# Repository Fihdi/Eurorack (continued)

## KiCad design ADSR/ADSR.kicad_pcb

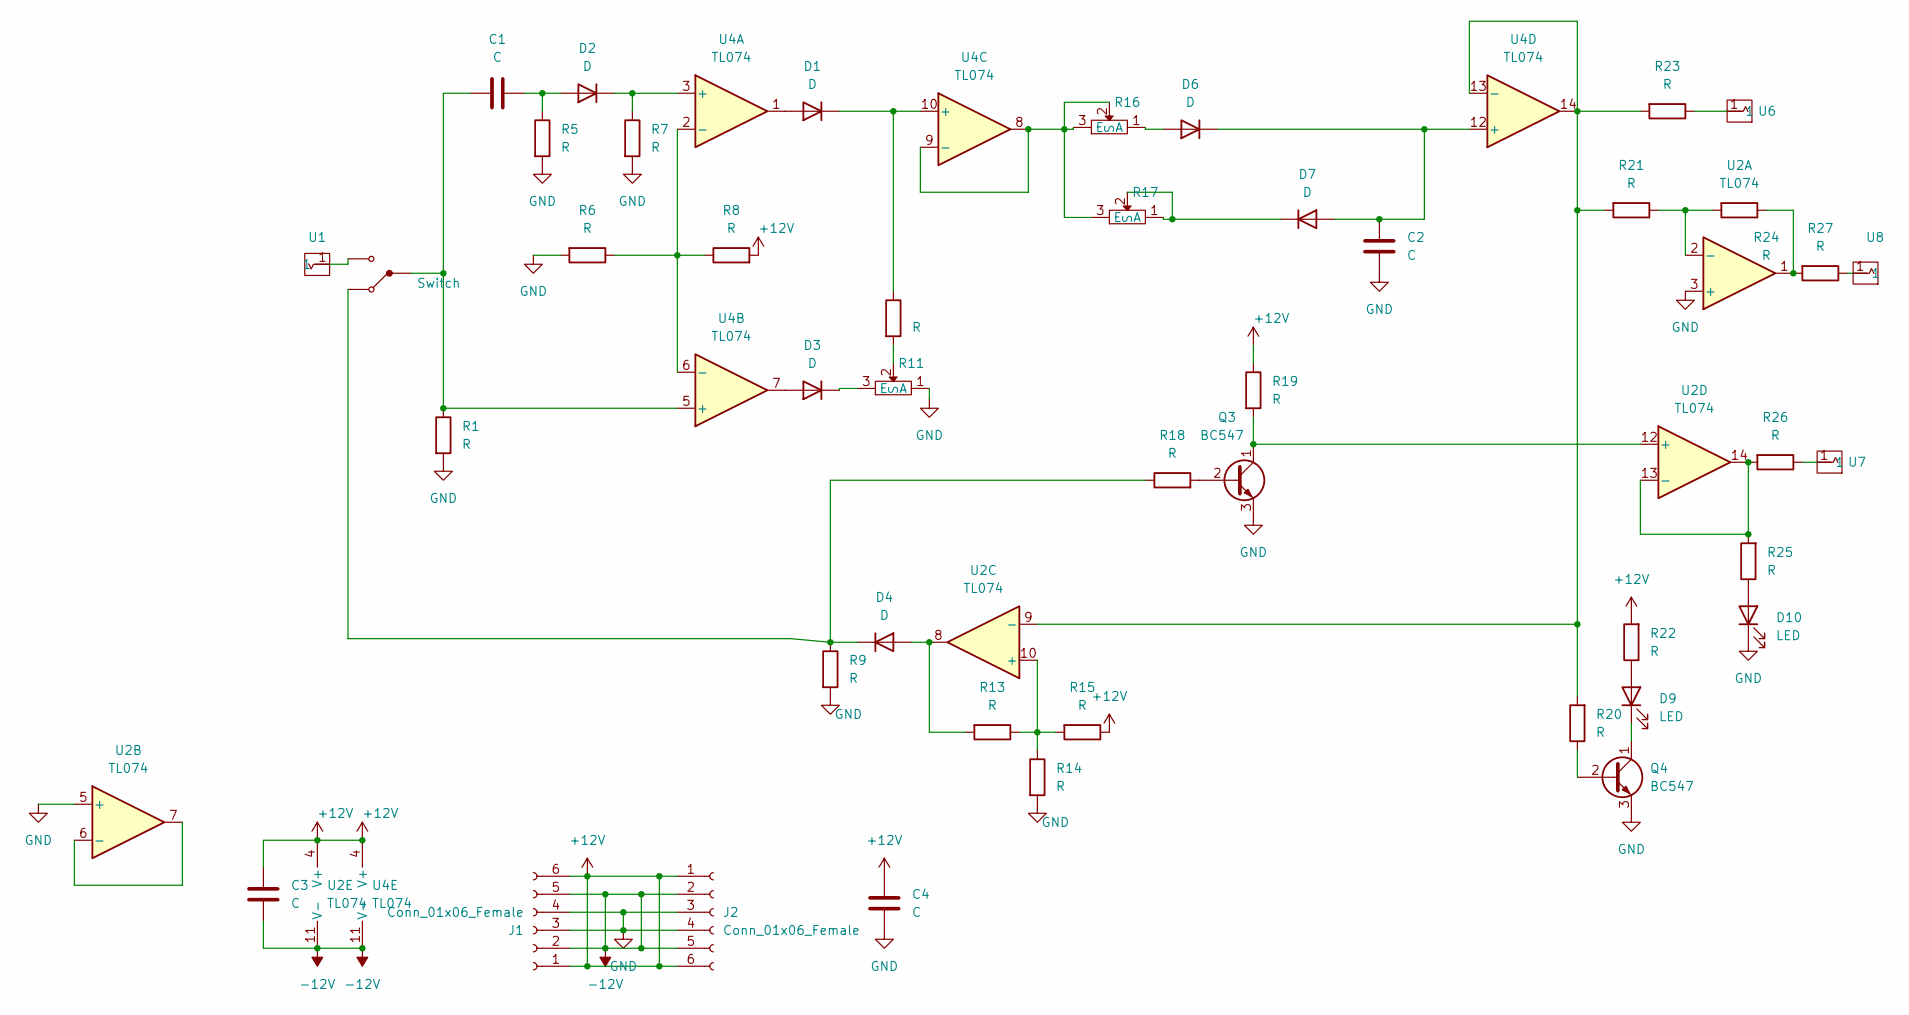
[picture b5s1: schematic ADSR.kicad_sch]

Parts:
C1, C3: C; C_Axial_L3.8mm_D2.6mm_P7.50mm_Horizontal
C2, C4: C; C_Axial_L3.8mm_D2.6mm_P10.00mm_Horizontal
D1, D2, D3, D4, D6, D7: D; D_A-405_P5.08mm_Vertical_AnodeUp
D9, D10: LED; LED_D5.0mm
J1, J2: Conn_01x06_Female; PinHeader_1x06_P2.54mm_Vertical
Q3, Q4: BC547; TO-92L_Inline_Wide
R1, R5, R6, R7, R8, R9, R10, R13, R14, R15, R18, R19, R20, R21, R22, R23, R24, R25, R26, R27: R; R_Axial_DIN0204_L3.6mm_D1.6mm_P7.62mm_Horizontal
R11, R16, R17: AlpsPot
U1, U6, U7, U8: Aux_flush; aux_flush
U2, U4: TL074; DIP-14_W7.62mm
U3: Switch

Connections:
+12V: C3.2, C4.2, J1.1, J1.6, J2.1, J2.6, R8.2, R15.1, R19.1, R22.2, U2.4 (V+), U4.4 (V+)
-12V: C3.1, J1.2, J1.5, J2.2, J2.5, U2.11 (V-), U4.11 (V-)
GND: C2.1, C4.1, D10.1 (K), J1.3, J1.4, J2.3, J2.4, Q3.3 (E), Q4.3 (E), R1.2, R5.2, R6.2, R7.2, R9.2, R11.1 (A), R14.2, U2.3 (+), U2.5 (+)
unnamed: D1.2 (A), U4.1
unnamed: D1.1 (K), R10.1, U4.10 (+)
unnamed: C1.2, D2.2 (A), R5.1
unnamed: D2.1 (K), R7.1, U4.3 (+)
unnamed: D3.2 (A), U4.7
unnamed: D3.1 (K), R11.3 (E)
unnamed: D4.2 (A), R13.2, U2.8
unnamed: D4.1 (K), R9.1, R18.1, U3.1
unnamed: D6.2 (A), R16.1 (A)
unnamed: C2.2, D6.1 (K), D7.2 (A), U4.12 (+)
unnamed: D7.1 (K), R17.1 (A), R17.2 (S)
unnamed: D9.2 (A), R22.1
unnamed: D9.1 (K), Q4.1 (C)
unnamed: D10.2 (A), R25.1
unnamed: Q3.2 (B), R18.2
unnamed: Q3.1 (C), R19.2, U2.12 (+)
unnamed: Q4.2 (B), R20.1
unnamed: R10.2, R11.2 (S)
unnamed: R16.2 (S), R16.3 (E), R17.3 (E), U4.8, U4.9 (-)
unnamed: R23.1, U6.1
unnamed: R24.1, R27.2, U2.1
unnamed: R26.1, U7.1
unnamed: R27.1, U8.1
unnamed: U1.1, U3.3
unnamed: R21.1, R24.2, U2.2 (-)
unnamed: U2.6 (-), U2.7
unnamed: R13.1, R14.1, R15.2, U2.10 (+)
unnamed: R20.2, R21.2, R23.2, U2.9 (-), U4.13 (-), U4.14
unnamed: R25.2, R26.2, U2.13 (-), U2.14
unnamed: R6.1, R8.1, U4.2 (-), U4.6 (-)
unnamed: C1.1, R1.1, U3.2, U4.5 (+)

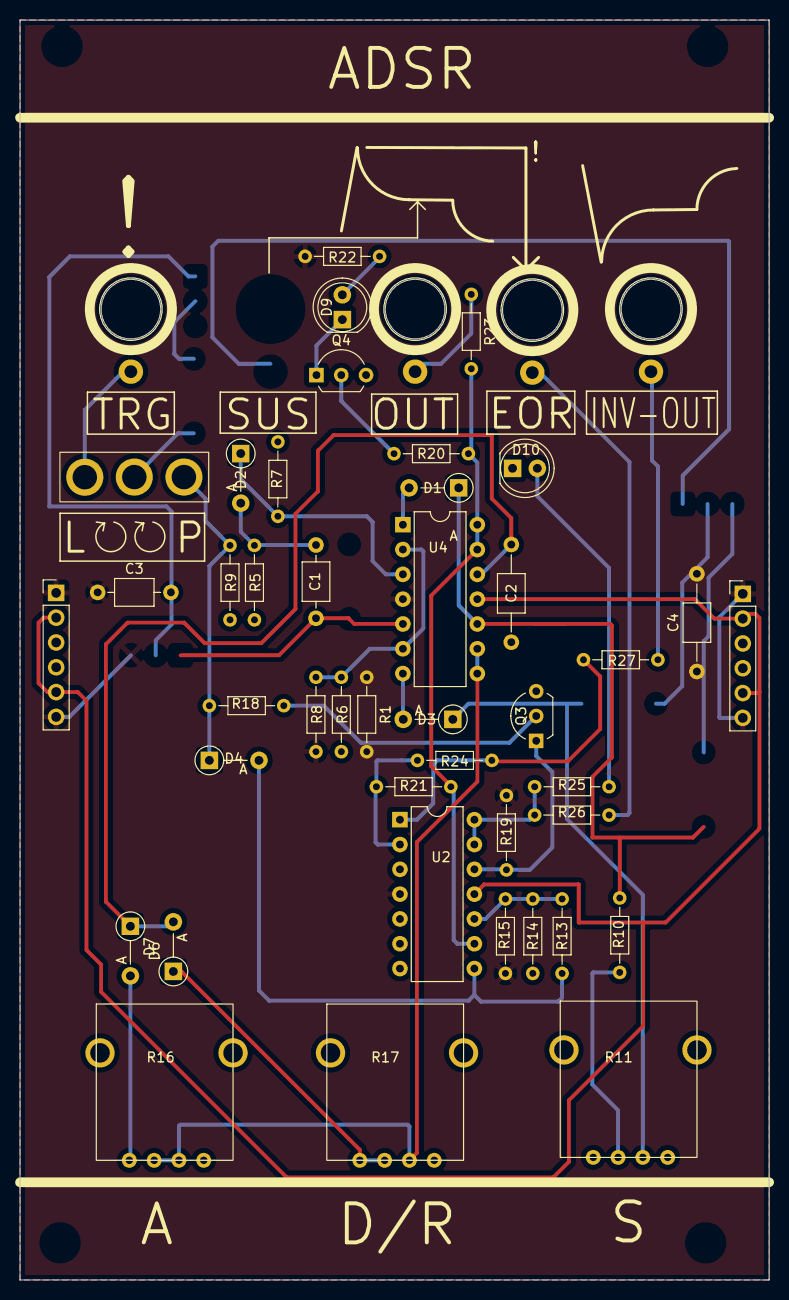
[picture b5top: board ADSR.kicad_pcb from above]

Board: 2 copper layers, 76.7 x 129.0 mm, 46 parts (0 on the bottom side), 34 nets.

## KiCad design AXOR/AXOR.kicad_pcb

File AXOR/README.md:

AXOR (Analogue XOR)

Improved stand-alone module of my analogue XOR circuit for CV intermangling, rectification or ring modulation purposes. XORing two square wave signals together results in an ringmodulation-like effect.

Incoming signals can be in the audio or in the low frequency range, including DC voltages. The signals are passed through VCAs before going to the AXOR circuit, these VCAs can also be bypassed via switches.

The core of this circuit is a subtractor followed by a full wave rectifier, the transfer function G for the CV OUT output is thus:

Example: IN1 and IN2 are square wave in the range of 0V - 5V:

The resulting truth table is the same as that of an XOR gate.

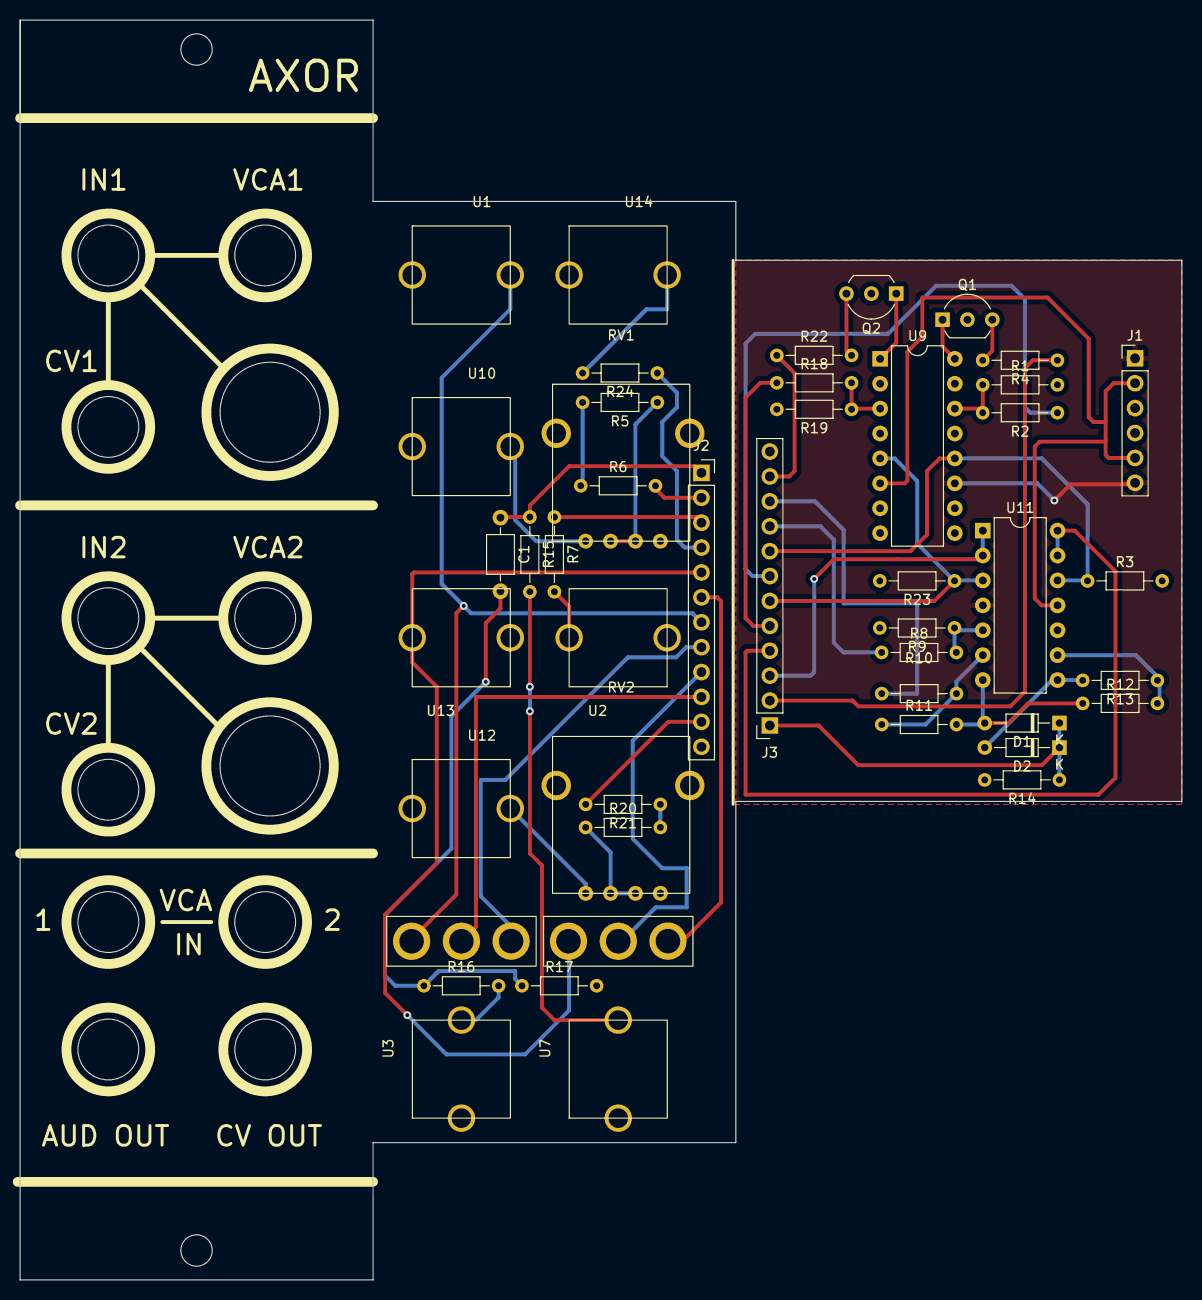
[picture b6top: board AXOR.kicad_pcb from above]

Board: 2 copper layers, 118.5 x 128.5 mm, 46 parts (0 on the bottom side), 36 nets.

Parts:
C1: 470n; C_Axial_L3.8mm_D2.6mm_P7.50mm_Horizontal
D1, D2: D; D_DO-34_SOD68_P7.62mm_Horizontal
J1: Conn_01x06_Pin; PinHeader_1x06_P2.54mm_Vertical
J2, J3: Conn_01x12_Pin; PinSocket_1x12_P2.54mm_Vertical
Q1, Q2: BC557; TO-92_Inline_Wide
R1, R5, R6, R7, R15, R16, R19, R20, R21, R24: 1k; R_Axial_DIN0204_L3.6mm_D1.6mm_P7.62mm_Horizontal
R2, R8, R9, R10, R11, R12, R13, R14, R17, R18: 100k; R_Axial_DIN0204_L3.6mm_D1.6mm_P7.62mm_Horizontal
R3, R4, R22, R23: 10k; R_Axial_DIN0204_L3.6mm_D1.6mm_P7.62mm_Horizontal
RV1, RV2: R_Potentiometer; AlpsPot
SW1, SW2: SW_SPDT; Switch
U1, U2, U3, U7, U10, U12, U13, U14: Aux_flush; 3mm5 Mono Aux
U9: LM13700; DIP-16_W7.62mm
U11: TL074; DIP-14_W7.62mm

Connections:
+12V: J1.1, J1.6, U9.11 (V+), U11.4 (V+)
-12V: J1.2, J1.5, U9.6 (V-), U11.11 (V-)
A1: J2.10, J3.10, R10.1, SW1.2 (B)
A2: J2.9, J3.9, R8.1, SW2.2 (B)
ABC1: J2.2, J3.2, R4.1, R6.2
ABC2: J2.11, J3.11, R21.2, R22.1
GND: J1.3, J1.4, J2.12, J3.12, Q1.2 (B), Q2.2 (B), R1.2, R3.2, R9.2, R14.2, R17.2, R19.2, R23.2, U9.4 (-), U9.13 (-), U11.10 (+)
IN1: J2.7, J3.7, R2.1, SW1.1 (A), U1.1
IN2: J2.5, J3.5, R18.1, SW2.1 (A), U13.1
unnamed: C1.2, R16.1, R17.1
unnamed: D1.2 (A), R11.2, R12.1, U11.7
unnamed: D2.2 (A), R13.2, U11.8
unnamed: Q1.1 (C), U9.16
unnamed: Q1.3 (E), R4.2
unnamed: Q2.1 (C), U9.1
unnamed: Q2.3 (E), R22.2
unnamed: R5.1, RV1.2, RV1.3
unnamed: R5.2, R6.1
unnamed: R7.2, U2.1
unnamed: R15.2, U7.1
unnamed: R16.2, U3.1
unnamed: R20.1, RV2.2, RV2.3
unnamed: R20.2, R21.1
unnamed: R24.2, U14.1
unnamed: RV1.1, U10.1
unnamed: RV2.1, U12.1
unnamed: R1.1, R2.2, U9.14 (+)
unnamed: R18.2, R19.1, U9.3 (+)
unnamed: R8.2, R9.1, U11.5 (+)
unnamed: R10.2, R11.1, U11.6 (-)
unnamed: R12.2, R13.1, U11.9 (-)
OUT: C1.1, D1.1 (K), D2.1 (K), J2.1, J3.1, R14.1, R15.1
OUT1: J2.4, J3.4, R24.1, U11.13 (-), U11.14
OUT2: J2.3, J3.3, R7.1, U11.1, U11.2 (-)
VCA1: J2.8, J3.8, R3.1, SW1.3 (C), U9.12, U11.12 (+)
VCA2: J2.6, J3.6, R23.1, SW2.3 (C), U9.5, U11.3 (+)

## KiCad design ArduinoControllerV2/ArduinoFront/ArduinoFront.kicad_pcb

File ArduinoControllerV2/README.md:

Versatile module that can be programmed to output 3 CV/Gate or sound signals.

No USB Interface from the front.

I used multiple TL072s instead of TL074 because that's what I got on hand at the time I designed this module.

Code mostly created by ChatGPT

Issue: No issues, the module is just very big for what it can do. Building MIDI-INT instead and programming it to behave as the arduino controller (or leave it as a MIDI Interface) would save a lot of space. Downside: No Inputs.

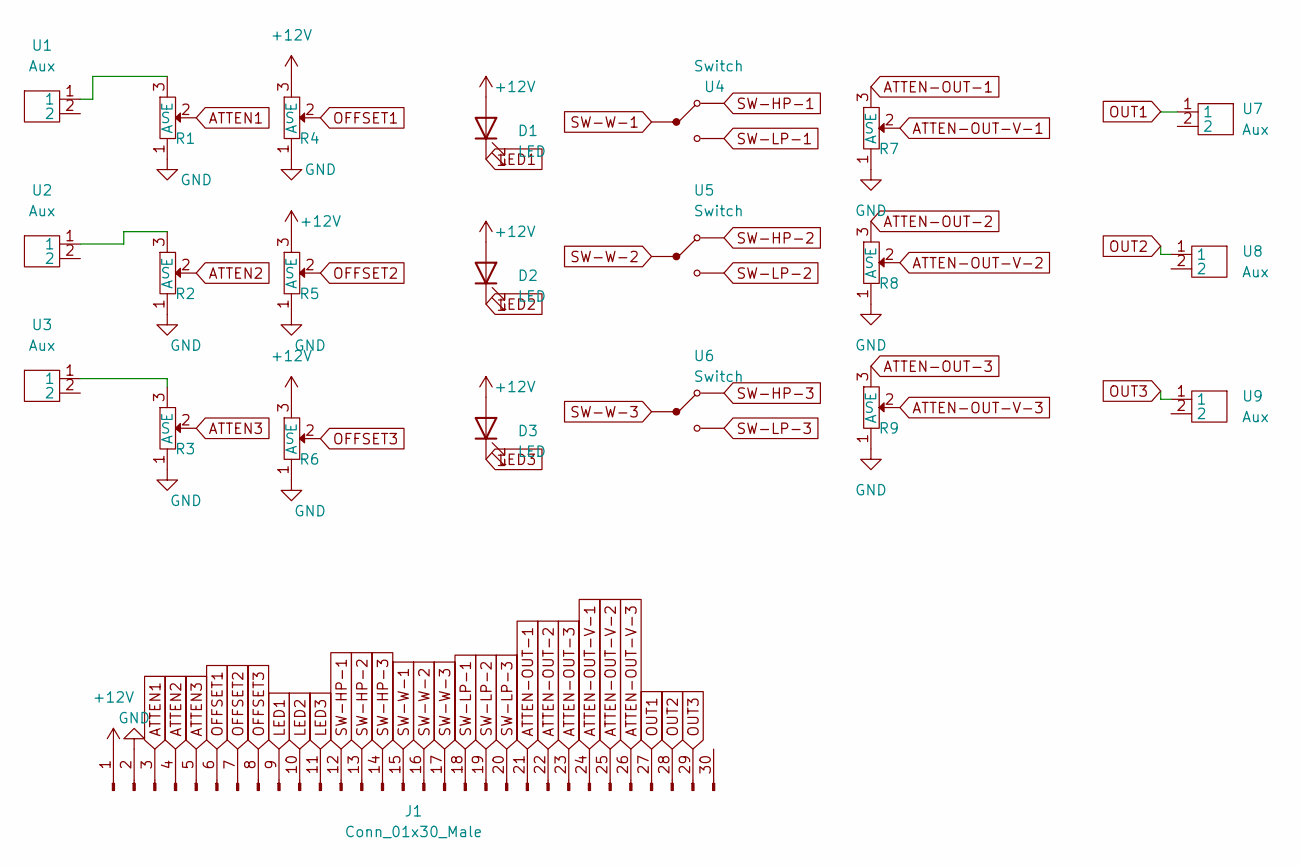
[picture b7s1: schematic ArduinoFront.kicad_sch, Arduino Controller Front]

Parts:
D1, D2, D3: LED; LED_D5.0mm
J1: Conn_01x30_Male; PinHeader_1x30_P2.54mm_Vertical
R1, R2, R3, R4, R5, R6, R7, R8, R9: AlpsPot
U1, U2, U3, U7, U8, U9: Aux; aux_flush
U4, U5, U6: Switch

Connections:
+12V: D1.2 (A), D2.2 (A), D3.2 (A), J1.1, R4.3 (E), R5.3 (E), R6.3 (E)
ATTEN1: J1.3, R1.2 (S)
ATTEN2: J1.4, R2.2 (S)
ATTEN3: J1.5, R3.2 (S)
ATTEN-OUT-1: J1.21, R7.3 (E)
ATTEN-OUT-2: J1.22, R8.3 (E)
ATTEN-OUT-3: J1.23, R9.3 (E)
ATTEN-OUT-V-1: J1.24, R7.2 (S)
ATTEN-OUT-V-2: J1.25, R8.2 (S)
ATTEN-OUT-V-3: J1.26, R9.2 (S)
GND: J1.2, R1.1 (A), R2.1 (A), R3.1 (A), R4.1 (A), R5.1 (A), R6.1 (A), R7.1 (A), R8.1 (A), R9.1 (A)
LED1: D1.1 (K), J1.9
LED2: D2.1 (K), J1.10
LED3: D3.1 (K), J1.11
unnamed: R1.3 (E), U1.1
unnamed: R2.3 (E), U2.1
unnamed: R3.3 (E), U3.1
OFFSET1: J1.6, R4.2 (S)
OFFSET2: J1.7, R5.2 (S)
OFFSET3: J1.8, R6.2 (S)
OUT1: J1.27, U7.1
OUT2: J1.28, U8.1
OUT3: J1.29, U9.1
SW-HP-1: J1.12, U4.1
SW-HP-2: J1.13, U5.1
SW-HP-3: J1.14, U6.1
SW-LP-1: J1.18, U4.3
SW-LP-2: J1.19, U5.3
SW-LP-3: J1.20, U6.3
SW-W-1: J1.15, U4.2
SW-W-2: J1.16, U5.2
SW-W-3: J1.17, U6.2

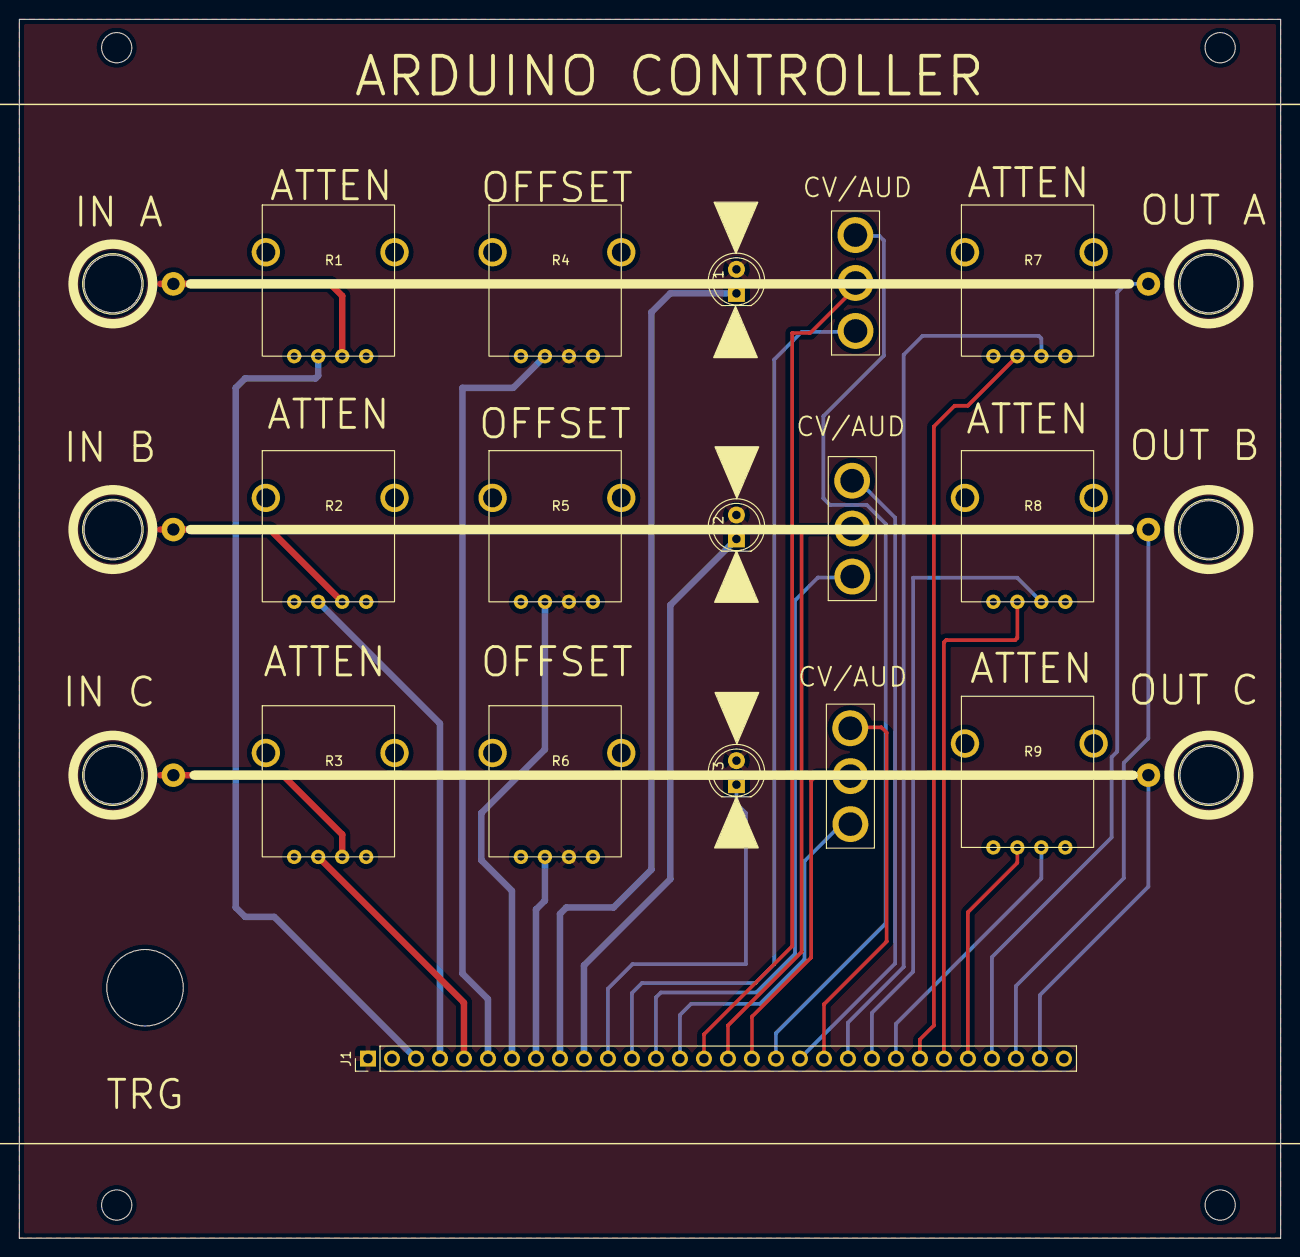
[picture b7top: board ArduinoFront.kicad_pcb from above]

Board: 2 copper layers, 133.5 x 129.0 mm, 22 parts (0 on the bottom side), 32 nets.

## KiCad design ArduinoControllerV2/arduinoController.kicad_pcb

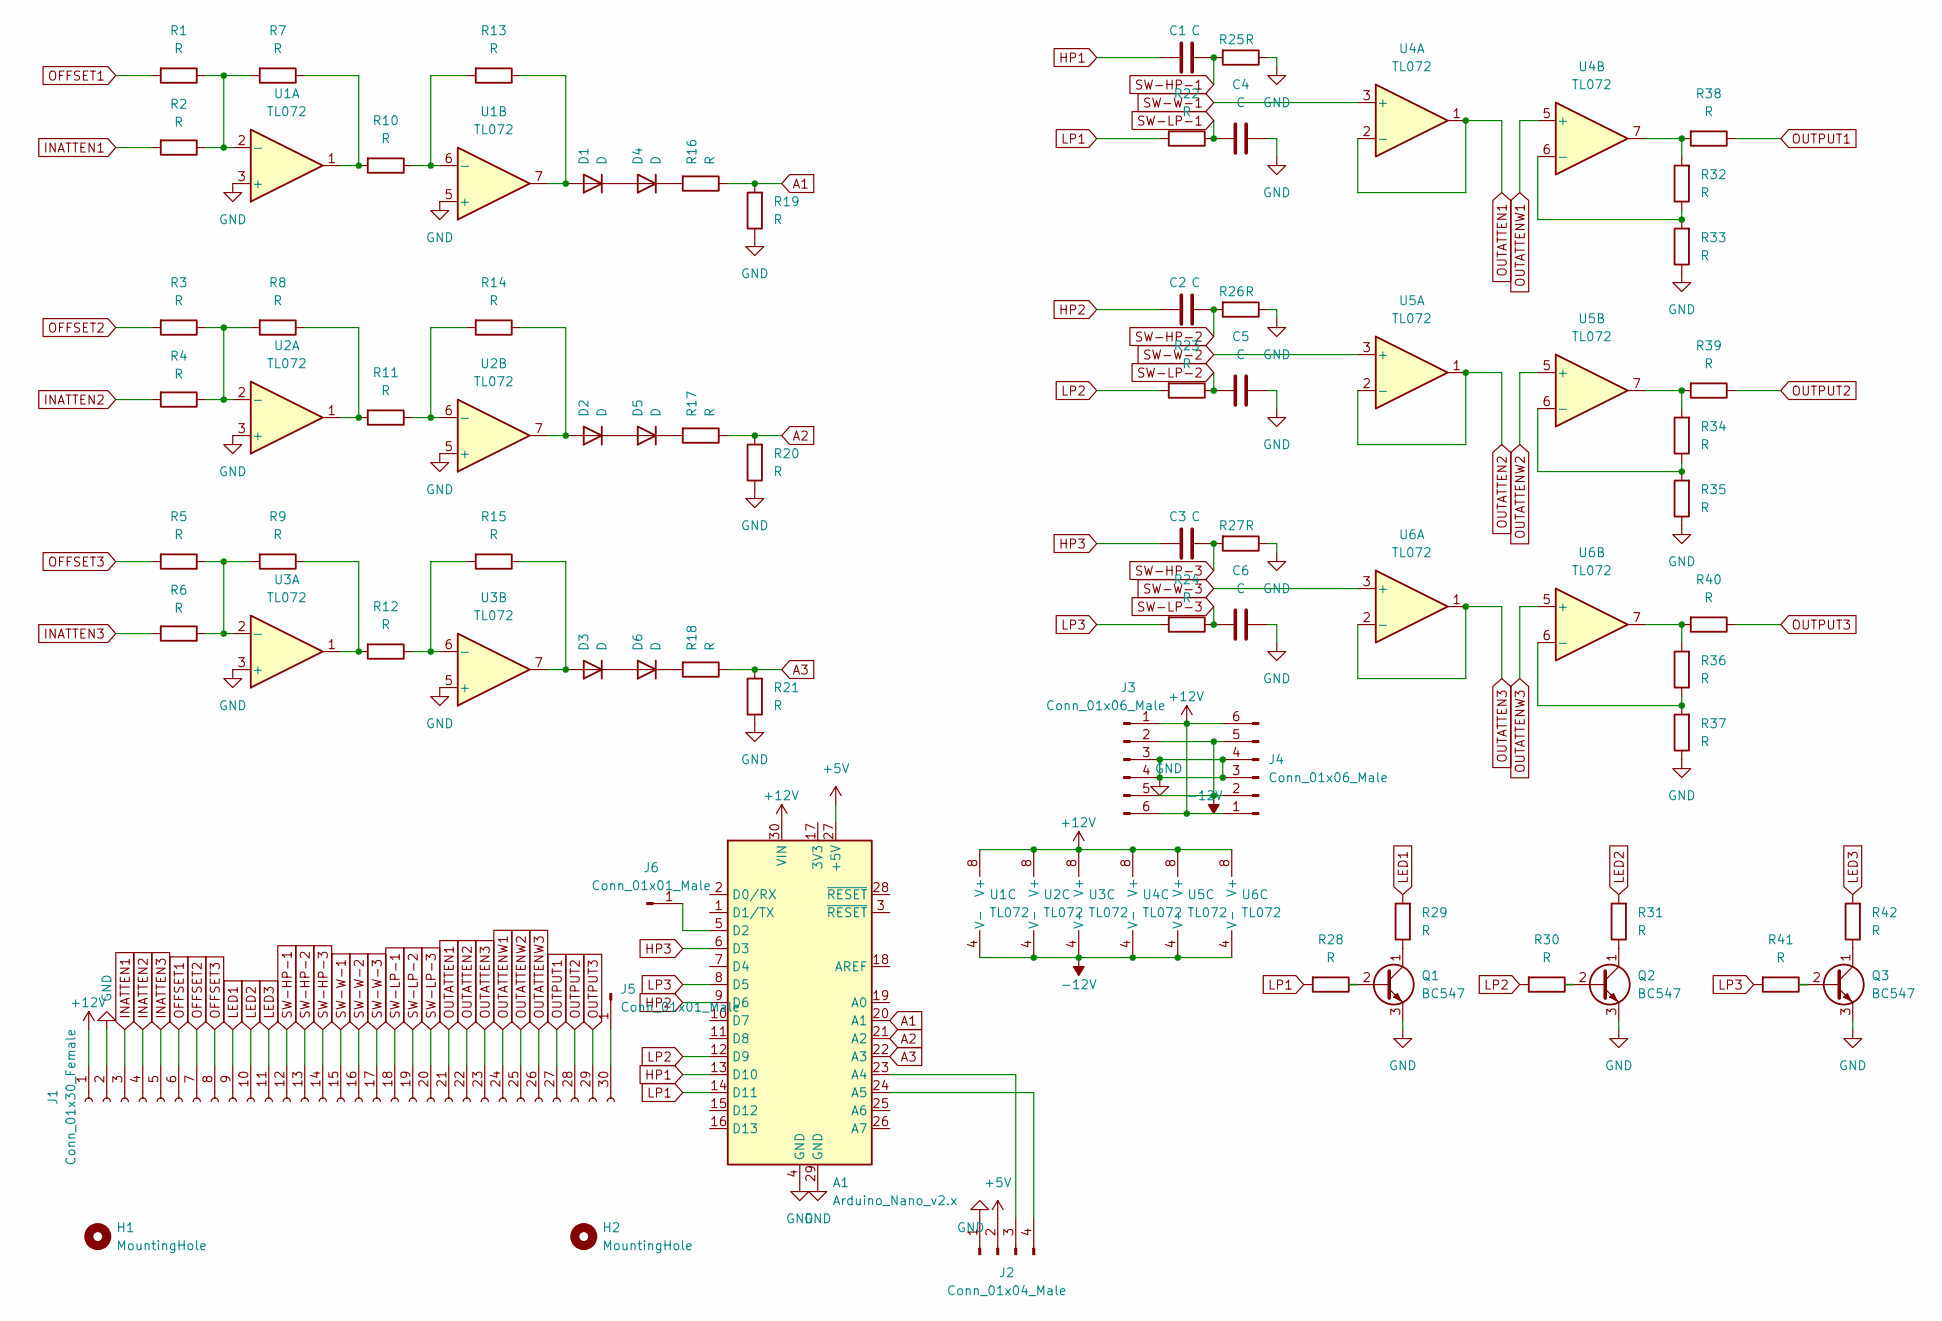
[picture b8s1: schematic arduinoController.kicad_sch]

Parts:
A1: Arduino_Nano_v2.x; Arduino_Nano
C1, C2, C3, C4, C5, C6: C; C_Axial_L5.1mm_D3.1mm_P7.50mm_Horizontal
D1, D2, D3, D4, D5, D6: D; D_A-405_P7.62mm_Horizontal
H1: MountingHole
H2: MountingHole; MountingHole_4.3mm_M4
J1: Conn_01x30_Female; PinHeader_1x30_P2.54mm_Vertical
J2: Conn_01x04_Male; PinHeader_1x04_P2.54mm_Vertical
J3, J4: Conn_01x06_Male; PinSocket_1x06_P2.54mm_Vertical
J5: Conn_01x01_Male; PinHeader_1x01_P2.54mm_Vertical
J6: Conn_01x01_Male
Q1, Q2, Q3: BC547; TO-92_Inline_Wide
R1, R2, R3, R4, R5, R6, R7, R8, R9, R10, R11, R12, R13, R14, R15, R16, R17, R18, R19, R20, R21, R22, R23, R24, R25, R26, R27, R28, R29, R30, R31, R32, R33, R34, R35, R36, R37, R38, R39, R40, R41, R42: R; R_Axial_DIN0207_L6.3mm_D2.5mm_P7.62mm_Horizontal
U1, U2, U3, U4, U5, U6: TL072; DIP-8_W7.62mm

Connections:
+5V: A1.27 (+5V), J2.2
+12V: A1.30 (VIN), J1.1, J3.1, J3.6, J4.1, J4.6, U1.8 (V+), U2.8 (V+), U3.8 (V+), U4.8 (V+), U5.8 (V+), U6.8 (V+)
-12V: J3.2, J3.5, J4.2, J4.5, U1.4 (V-), U2.4 (V-), U3.4 (V-), U4.4 (V-), U5.4 (V-), U6.4 (V-)
A1: A1.20 (A1), R16.1, R19.2
A2: A1.21 (A2), R17.1, R20.2
A3: A1.22 (A3), R18.1, R21.2
GND: A1.4 (GND), A1.29 (GND), C4.2, C5.2, C6.2, J1.2, J2.1, J3.3, J3.4, J4.3, J4.4, Q1.3 (E), Q2.3 (E), Q3.3 (E), R19.1, R20.1, R21.1, R25.1, R26.1, R27.1, R33.1, R35.1, R37.1, U1.3 (+), U1.5 (+), U2.3 (+), U2.5 (+), U3.3 (+), U3.5 (+)
HP1: A1.13 (D10), C1.1
HP2: A1.9 (D6), C2.1
HP3: A1.6 (D3), C3.1
INATTEN1: J1.3, R2.2
INATTEN2: J1.4, R4.2
INATTEN3: J1.5, R6.2
LED1: J1.9, R29.2
LED2: J1.10, R31.2
LED3: J1.11, R42.2
LP1: A1.14 (D11), R22.2, R28.2
LP2: A1.12 (D9), R23.2, R30.2
LP3: A1.8 (D5), R24.2, R41.2
unnamed: A1.5 (D2), J6.1
unnamed: A1.23 (A4), J2.3
unnamed: A1.24 (A5), J2.4
unnamed: D1.1 (K), D4.2 (A)
unnamed: D1.2 (A), R13.1, U1.7
unnamed: D2.1 (K), D5.2 (A)
unnamed: D2.2 (A), R14.1, U2.7
unnamed: D3.1 (K), D6.2 (A)
unnamed: D3.2 (A), R15.1, U3.7
unnamed: D4.1 (K), R16.2
unnamed: D5.1 (K), R17.2
unnamed: D6.1 (K), R18.2
unnamed: J1.30, J5.1
unnamed: Q1.1 (C), R29.1
unnamed: Q1.2 (B), R28.1
unnamed: Q2.1 (C), R31.1
unnamed: Q2.2 (B), R30.1
unnamed: Q3.1 (C), R42.1
unnamed: Q3.2 (B), R41.1
unnamed: R1.1, R2.1, R7.2, U1.2 (-)
unnamed: R3.1, R4.1, R8.2, U2.2 (-)
unnamed: R5.1, R6.1, R9.2, U3.2 (-)
unnamed: R10.1, R13.2, U1.6 (-)
unnamed: R7.1, R10.2, U1.1
unnamed: R11.1, R14.2, U2.6 (-)
unnamed: R8.1, R11.2, U2.1
unnamed: R12.1, R15.2, U3.6 (-)
unnamed: R9.1, R12.2, U3.1
unnamed: R32.1, R33.2, U4.6 (-)
unnamed: R32.2, R38.2, U4.7
unnamed: R34.1, R35.2, U5.6 (-)
unnamed: R34.2, R39.2, U5.7
unnamed: R36.1, R37.2, U6.6 (-)
unnamed: R36.2, R40.2, U6.7
OFFSET1: J1.6, R1.2
OFFSET2: J1.7, R3.2
OFFSET3: J1.8, R5.2
OUTATTEN1: J1.21, U4.1, U4.2 (-)
OUTATTEN2: J1.22, U5.1, U5.2 (-)
OUTATTEN3: J1.23, U6.1, U6.2 (-)
OUTATTENW1: J1.24, U4.5 (+)
OUTATTENW2: J1.25, U5.5 (+)
OUTATTENW3: J1.26, U6.5 (+)
OUTPUT1: J1.27, R38.1
OUTPUT2: J1.28, R39.1
OUTPUT3: J1.29, R40.1
SW-HP-1: C1.2, J1.12, R25.2
SW-HP-2: C2.2, J1.13, R26.2
SW-HP-3: C3.2, J1.14, R27.2
SW-LP-1: C4.1, J1.18, R22.1
SW-LP-2: C5.1, J1.19, R23.1
SW-LP-3: C6.1, J1.20, R24.1
SW-W-1: J1.15, U4.3 (+)
SW-W-2: J1.16, U5.3 (+)
SW-W-3: J1.17, U6.3 (+)

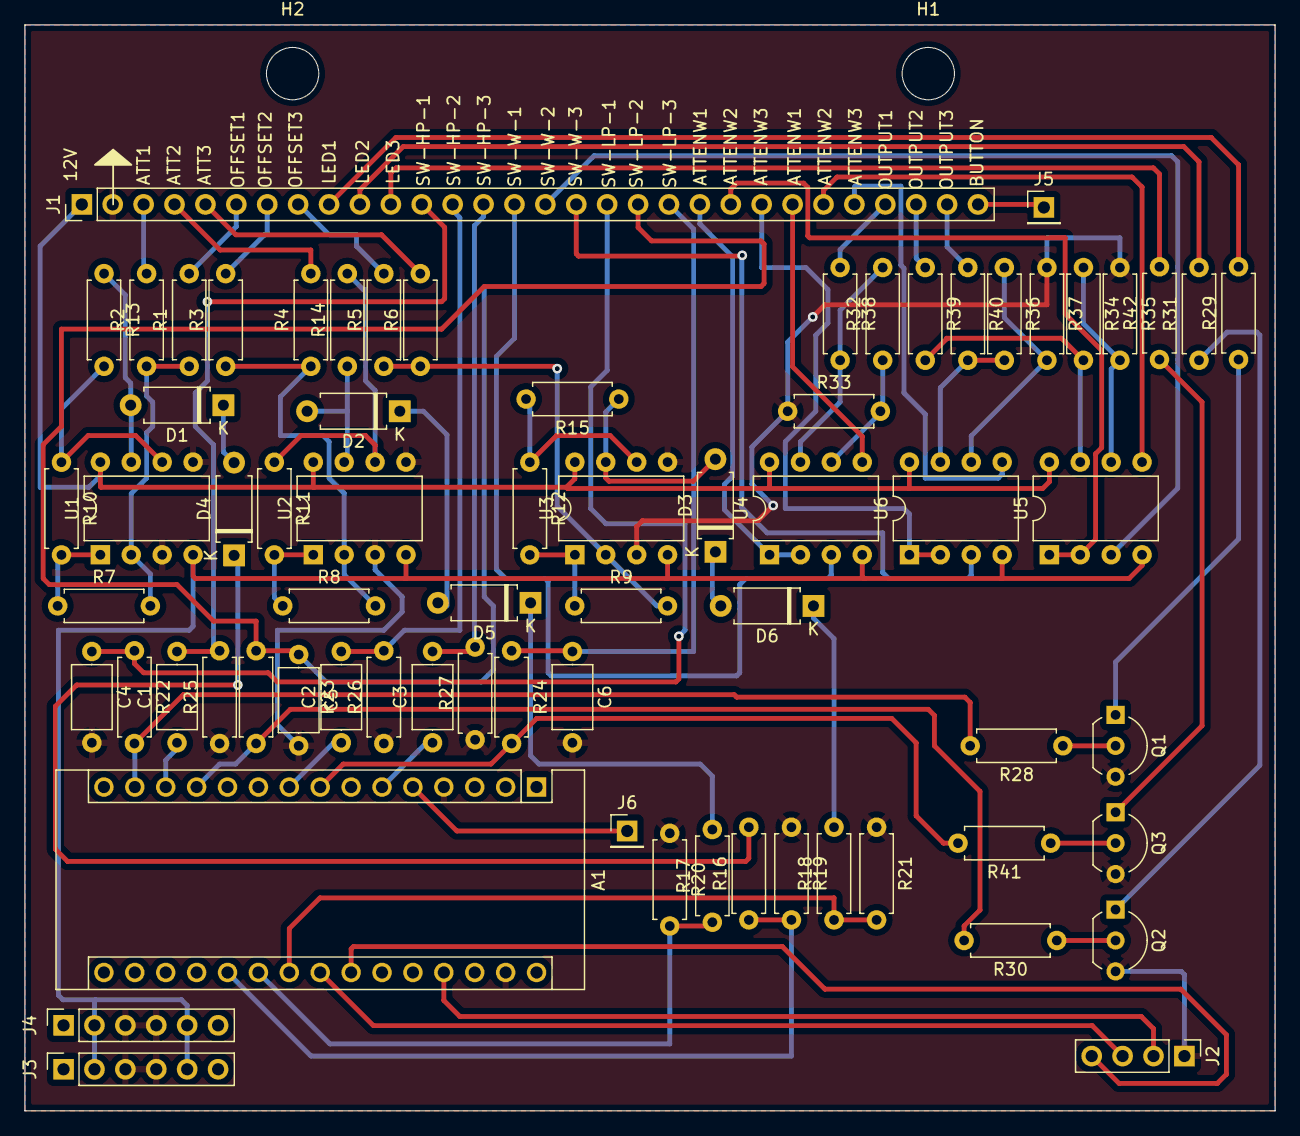
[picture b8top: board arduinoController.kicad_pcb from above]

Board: 2 copper layers, 102.8 x 89.2 mm, 72 parts (0 on the bottom side), 74 nets.
